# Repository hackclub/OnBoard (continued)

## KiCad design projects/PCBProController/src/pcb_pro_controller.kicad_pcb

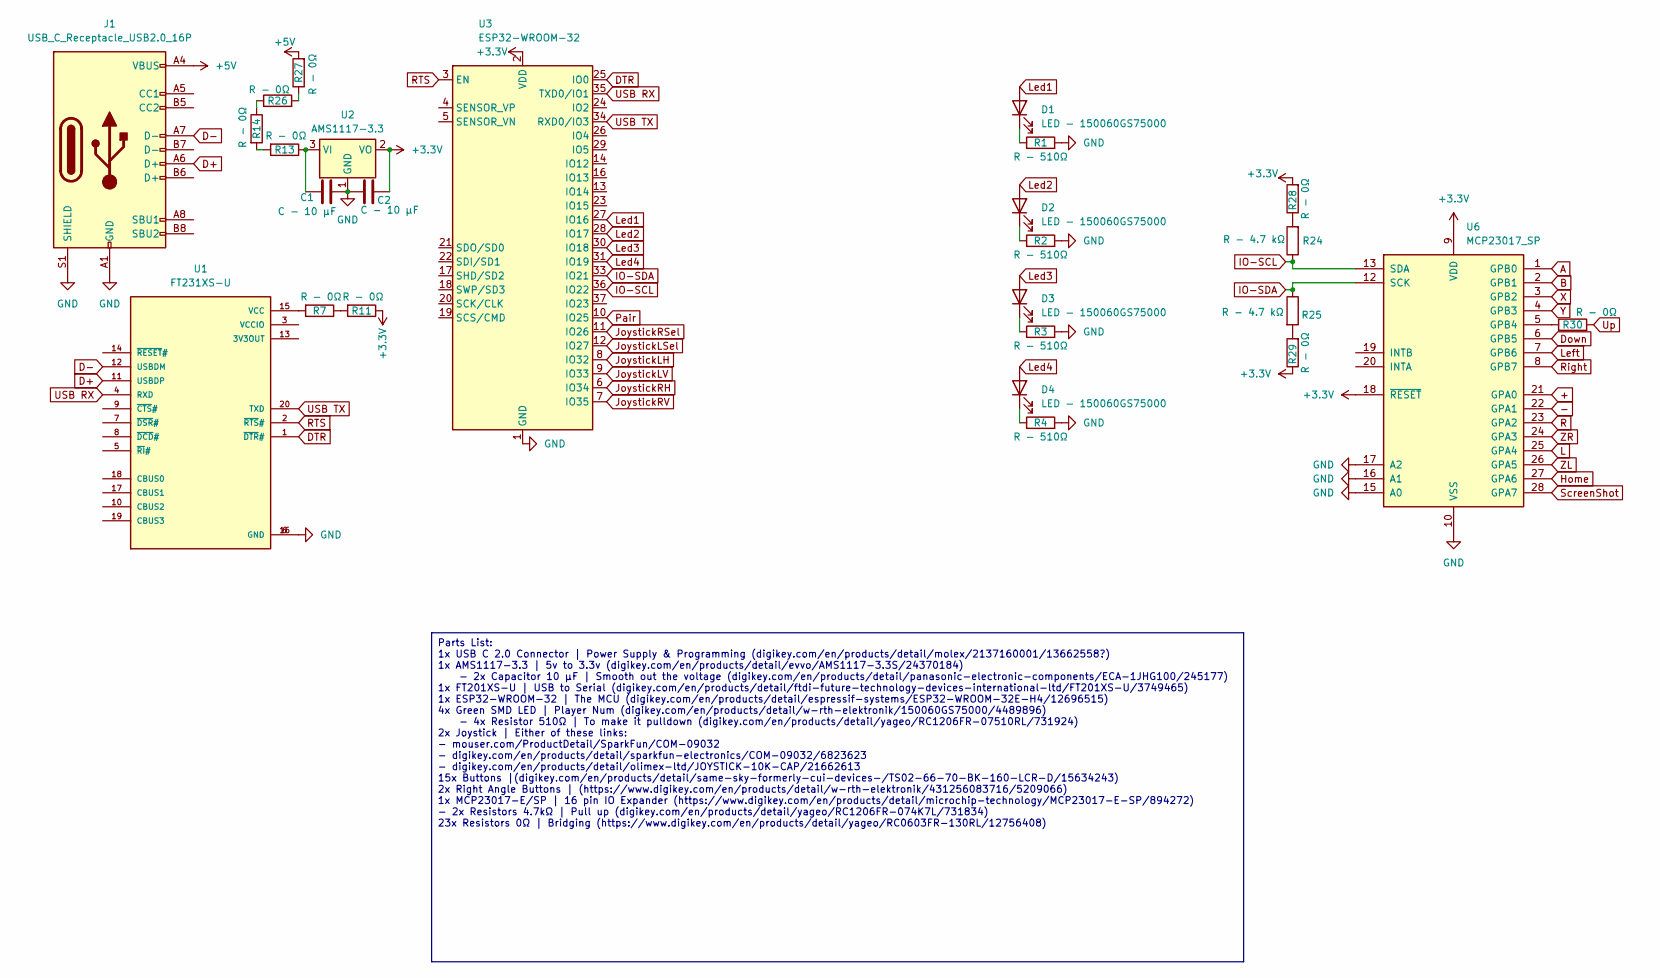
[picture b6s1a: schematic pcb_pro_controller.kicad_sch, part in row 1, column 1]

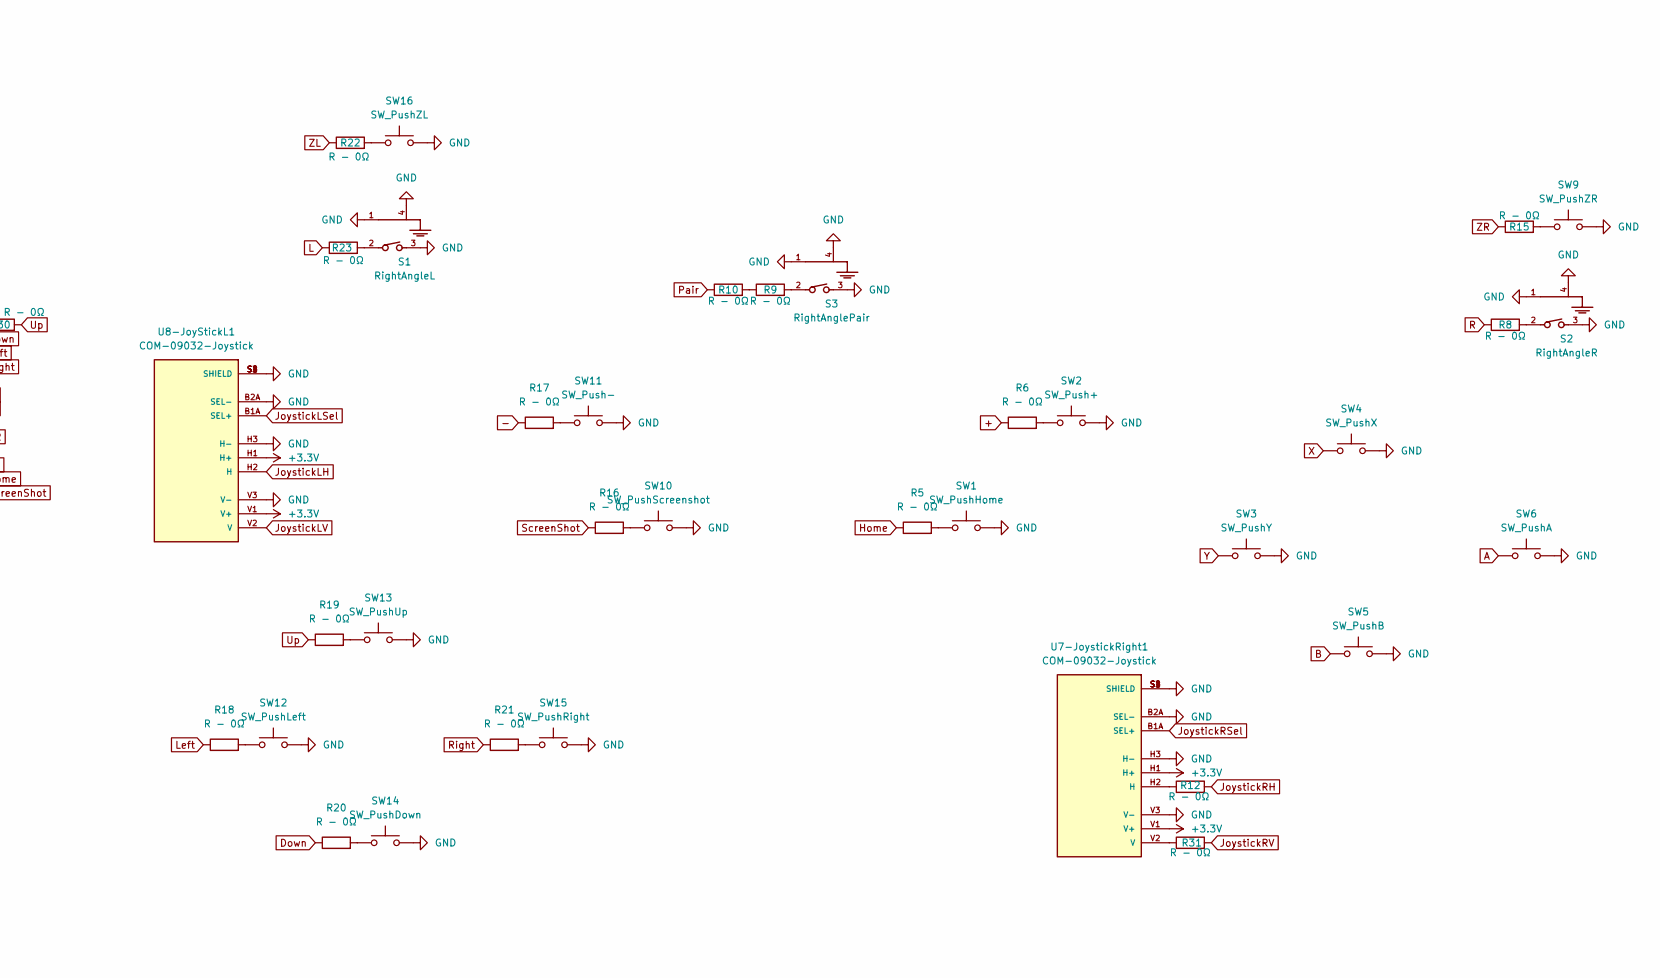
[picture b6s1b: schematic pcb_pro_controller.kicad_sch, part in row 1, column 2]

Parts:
C1, C2: C - 10 µF; CP_Radial_D5.0mm_P2.00mm
D1, D2, D3, D4: LED - 150060GS75000; LED_0603_1608Metric_Pad1.05x0.95mm_HandSolder
J1: USB_C_Receptacle_USB2.0_16P; USB_C_Receptacle_GCT_USB4085
R1, R2, R3, R4: R - 510Ω; R_1206_3216Metric_Pad1.30x1.75mm_HandSolder
R5, R6, R7, R8, R9, R10, R11, R12, R13, R14, R15, R16, R17, R18, R19, R20, R21, R22, R23, R26, R27, R28, R29, R30, R31: R - 0Ω; R_0603_1608Metric_Pad0.98x0.95mm_HandSolder
R24, R25: R - 4.7 kΩ; R_1206_3216Metric_Pad1.30x1.75mm_HandSolder
S1: RightAngleL; 4312560837X6; PART-NUMBER 431256083716
S2: RightAngleR; 4312560837X6; PART-NUMBER 431256083716
S3: RightAnglePair; 4312560837X6; PART-NUMBER 431256083716
SW1: SW_PushHome; SW_PUSH_6mm_H5mm
SW2: SW_Push+; SW_PUSH_6mm_H5mm
SW3: SW_PushY; SW_PUSH_6mm_H5mm
SW4: SW_PushX; SW_PUSH_6mm_H5mm
SW5: SW_PushB; SW_PUSH_6mm_H5mm
SW6: SW_PushA; SW_PUSH_6mm_H5mm
SW9: SW_PushZR; SW_PUSH_6mm_H5mm
SW10: SW_PushScreenshot; SW_PUSH_6mm_H5mm
SW11: SW_Push-; SW_PUSH_6mm_H5mm
SW12: SW_PushLeft; SW_PUSH_6mm_H5mm
SW13: SW_PushUp; SW_PUSH_6mm_H5mm
SW14: SW_PushDown; SW_PUSH_6mm_H5mm
SW15: SW_PushRight; SW_PUSH_6mm_H5mm
SW16: SW_PushZL; SW_PUSH_6mm_H5mm
U1: FT231XS-U; SOP63P599X175-20N; PARTREV 1.2
U2: AMS1117-3.3; SOT-223-3_TabPin2
U3: ESP32-WROOM-32
U6: MCP23017_SP; DIP-28_W7.62mm
U7-JoystickRight1, U8-JoyStickL1: COM-09032-Joystick; XDCR_COM-09032; PARTREV N/A

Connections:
+: R6.1, U6.21 (GPA0)
+3.3V: C2.1, R11.1, R28.2, R29.1, U2.2 (VO), U3.2 (VDD), U6.9 (VDD), U6.18 (~RESET), U7-JoystickRight1.H1 (H+), U7-JoystickRight1.V1 (V+), U8-JoyStickL1.H1 (H+), U8-JoyStickL1.V1 (V+)
+5V: J1.A4 (VBUS), J1.A9 (VBUS), J1.B4 (VBUS), J1.B9 (VBUS), R27.2
-: R17.1, U6.22 (GPA1)
A: SW6.1, U6.1 (GPB0)
B: SW5.1, U6.2 (GPB1)
D+: J1.A6 (D+), U1.11 (USBDP)
D-: J1.A7 (D-), U1.12 (USBDM)
DTR: U1.1 (~DTR#), U3.25 (IO0)
Down: R20.1, U6.6 (GPB5)
GND: C1.2, C2.2, J1.A1 (GND), J1.A12 (GND), J1.B1 (GND), J1.B12 (GND), J1.S1 (SHIELD), R1.2, R2.2, R3.2, R4.2, S1.1, S1.3, S1.4, S2.1, S2.3, S2.4, S3.1, S3.3, S3.4, SW1.2, SW2.2, SW3.2, SW4.2, SW5.2, SW6.2, SW9.2, SW10.2, SW11.2, SW12.2, SW13.2, SW14.2, SW15.2, SW16.2, U1.6 (GND), U1.16 (GND), U2.1 (GND), U3.1 (GND), U3.15 (GND), U3.38 (GND), U3.39 (GND), U6.10 (VSS), U6.15 (A0), U6.16 (A1), U6.17 (A2), U7-JoystickRight1.B2A (SEL-), U7-JoystickRight1.H3 (H-), U7-JoystickRight1.S1 (SHIELD), U7-JoystickRight1.S2 (SHIELD), U7-JoystickRight1.S3 (SHIELD), U7-JoystickRight1.S4 (SHIELD), U7-JoystickRight1.V3 (V-), U8-JoyStickL1.B2A (SEL-), U8-JoyStickL1.H3 (H-), U8-JoyStickL1.S1 (SHIELD), U8-JoyStickL1.S2 (SHIELD), U8-JoyStickL1.S3 (SHIELD), U8-JoyStickL1.S4 (SHIELD), U8-JoyStickL1.V3 (V-)
Home: R5.1, U6.27 (GPA6)
IO-SCL: R24.1, U3.36 (IO22), U6.13 (SDA)
IO-SDA: R25.1, U3.33 (IO21), U6.12 (SCK)
JoystickLH: U3.8 (IO32), U8-JoyStickL1.H2 (H)
JoystickLSel: U3.12 (IO27), U8-JoyStickL1.B1A (SEL+)
JoystickLV: U3.9 (IO33), U8-JoyStickL1.V2 (V)
JoystickRH: R12.2, U3.6 (IO34)
JoystickRSel: U3.11 (IO26), U7-JoystickRight1.B1A (SEL+)
JoystickRV: R31.2, U3.7 (IO35)
L: R23.1, U6.25 (GPA4)
Led1: D1.2 (A), U3.27 (IO16)
Led2: D2.2 (A), U3.28 (IO17)
Led3: D3.2 (A), U3.30 (IO18)
Led4: D4.2 (A), U3.31 (IO19)
Left: R18.1, U6.7 (GPB6)
unnamed: D1.1 (K), R1.1
unnamed: D2.1 (K), R2.1
unnamed: D3.1 (K), R3.1
unnamed: D4.1 (K), R4.1
unnamed: R5.2, SW1.1
unnamed: R6.2, SW2.1
unnamed: R8.2, S2.2
unnamed: R9.2, S3.2
unnamed: R9.1, R10.2
unnamed: R7.1, R11.2
unnamed: R13.2, R14.2
unnamed: R14.1, R26.1
unnamed: R15.2, SW9.1
unnamed: R16.2, SW10.1
unnamed: R17.2, SW11.1
unnamed: R18.2, SW12.1
unnamed: R19.2, SW13.1
unnamed: R20.2, SW14.1
unnamed: R21.2, SW15.1
unnamed: R22.2, SW16.1
unnamed: R23.2, S1.2
unnamed: R24.2, R28.1
unnamed: R25.2, R29.2
unnamed: R26.2, R27.1
unnamed: R7.2, U1.15 (VCC)
unnamed: C1.1, R13.1, U2.3 (VI)
unnamed: R30.1, U6.5 (GPB4)
unnamed: R12.1, U7-JoystickRight1.H2 (H)
unnamed: R31.1, U7-JoystickRight1.V2 (V)
Pair: R10.1, U3.10 (IO25)
R: R8.1, U6.23 (GPA2)
RTS: U1.2 (~RTS#), U3.3 (EN)
Right: R21.1, U6.8 (GPB7)
ScreenShot: R16.1, U6.28 (GPA7)
USB RX: U1.4 (RXD), U3.35 (TXD0/IO1)
USB TX: U1.20 (TXD), U3.34 (RXD0/IO3)
Up: R19.1, R30.2
X: SW4.1, U6.3 (GPB2)
Y: SW3.1, U6.4 (GPB3)
ZL: R22.1, U6.26 (GPA5)
ZR: R15.1, U6.24 (GPA3)

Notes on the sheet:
Parts List: 1x USB C 2.0 Connector | Power Supply & Programming (digikey.com/en/products/detail/molex/2137160001/13662558?) 1x AMS1117-3.3 | 5v to 3.3v (digikey.com/en/products/detail/evvo/AMS1117-3.3S/24370184) - 2x Capacitor 10 µF | Smooth out the voltage (digikey.com/en/products/detail/panasonic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

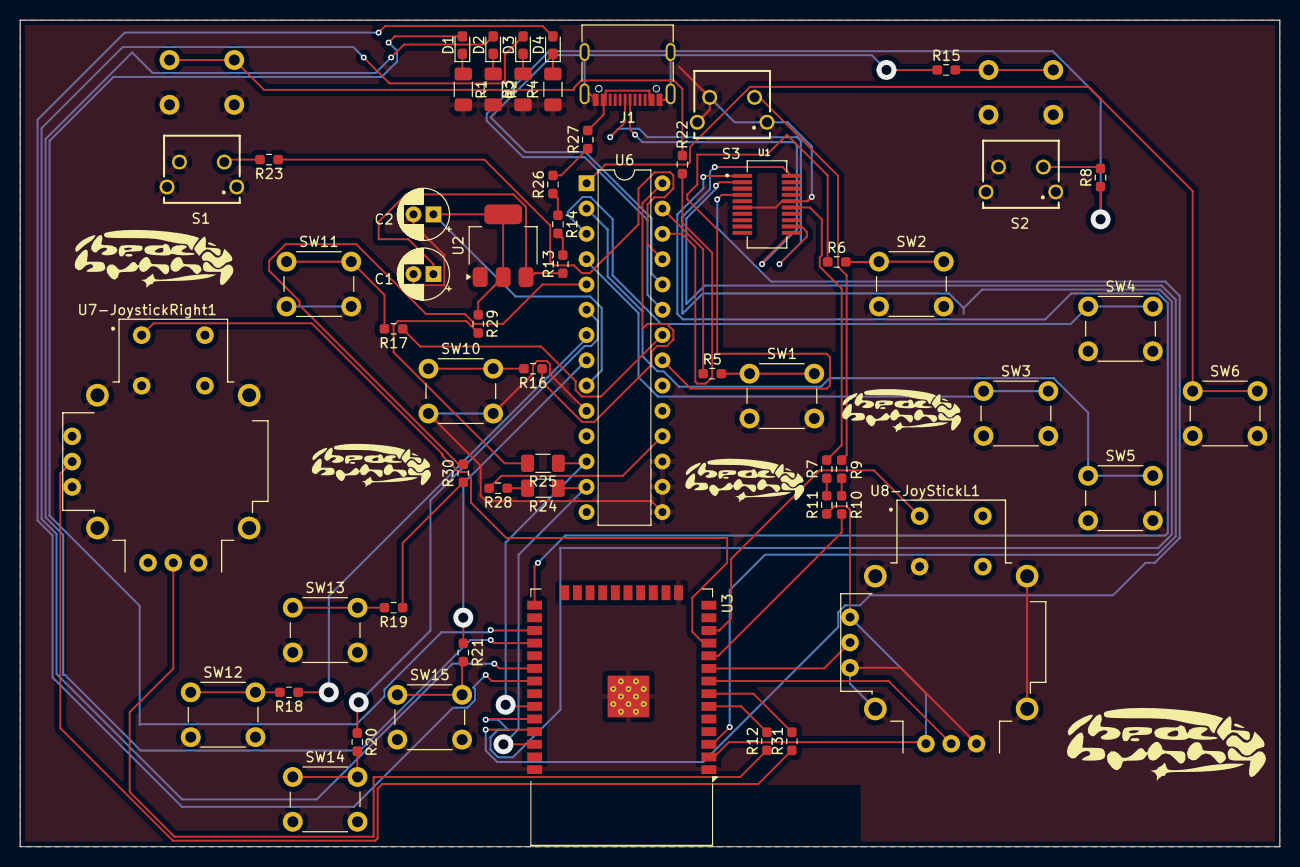
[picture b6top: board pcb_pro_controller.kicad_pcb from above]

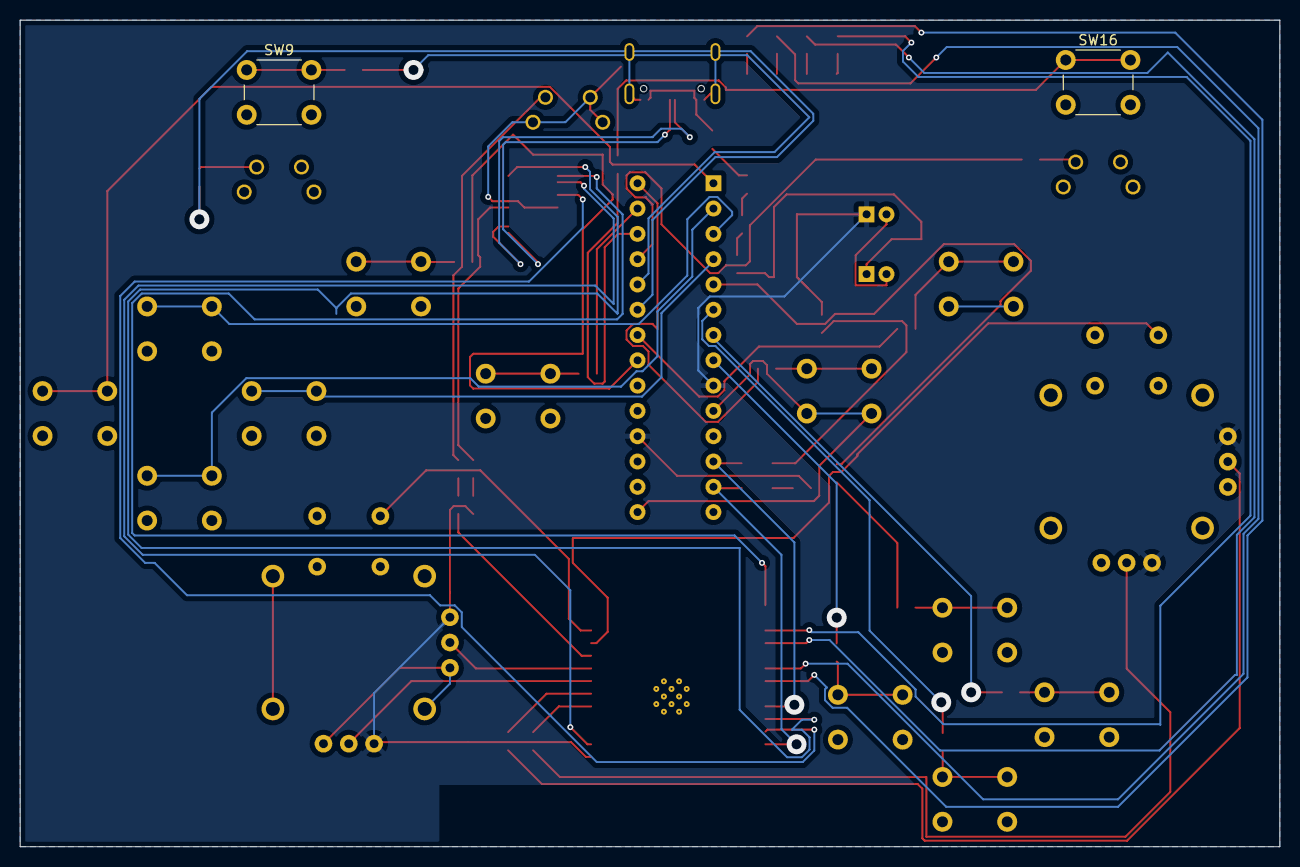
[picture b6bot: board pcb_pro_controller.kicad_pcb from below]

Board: 2 copper layers, 126.5 x 83.0 mm, 61 parts (2 on the bottom side), 67 nets.

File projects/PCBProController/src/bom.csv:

Designator,Footprint,Quantity,Value,LCSC Part #
"C1, C2",CP_Radial_D5.0mm_P2.00mm,2,C - 10 µF,
"D1, D2, D3, D4",0603,4,LED - 150060GS75000,
J1,USB_C_Receptacle_G-Switch_GT-USB-7010ASV,1,USB_C_Receptacle_USB2.0_16P,
"R1, R2, R3, R4",1206,4,R - 510Ω,
"R10, R11, R12, R13, R14, R15, R16, R17, R18, R19, R20, R21, R22, R23, R26, R27, R28, R29, R30, R31, R5, R6, R7, R8, R9",0603,25,R - 0Ω,
"R24, R25",1206,2,R - 4.7 kΩ,
S1,4312560837X6,1,RightAngleL,
S2,4312560837X6,1,RightAngleR,
S3,4312560837X6,1,RightAnglePair,
SW1,SW_PUSH_6mm_H5mm,1,SW_PushHome,
SW10,SW_PUSH_6mm_H5mm,1,SW_PushScreenshot,
SW11,SW_PUSH_6mm_H5mm,1,SW_Push-,
SW12,SW_PUSH_6mm_H5mm,1,SW_PushLeft,
SW13,SW_PUSH_6mm_H5mm,1,SW_PushUp,
SW14,SW_PUSH_6mm_H5mm,1,SW_PushDown,
SW15,SW_PUSH_6mm_H5mm,1,SW_PushRight,
SW16,SW_PUSH_6mm_H5mm,1,SW_PushZL,
SW2,SW_PUSH_6mm_H5mm,1,SW_Push+,
SW3,SW_PUSH_6mm_H5mm,1,SW_PushY,
SW4,SW_PUSH_6mm_H5mm,1,SW_PushX,
SW5,SW_PUSH_6mm_H5mm,1,SW_PushB,
SW6,SW_PUSH_6mm_H5mm,1,SW_PushA,
SW9,SW_PUSH_6mm_H5mm,1,SW_PushZR,
U1,SOP63P599X175-20N,1,FT231XS-R,
U2,SOT-223-3_TabPin2,1,AMS1117-3.3,
U3,ESP32-WROOM-32,1,ESP32-WROOM-32,
U6,DIP-28_W7.62mm,1,MCP23017_SP,
"U7-JOYSTICKRIGHT1, U8-JOYSTICKL1",XDCR_COM-09032,2,COM-09032-Joystick,
